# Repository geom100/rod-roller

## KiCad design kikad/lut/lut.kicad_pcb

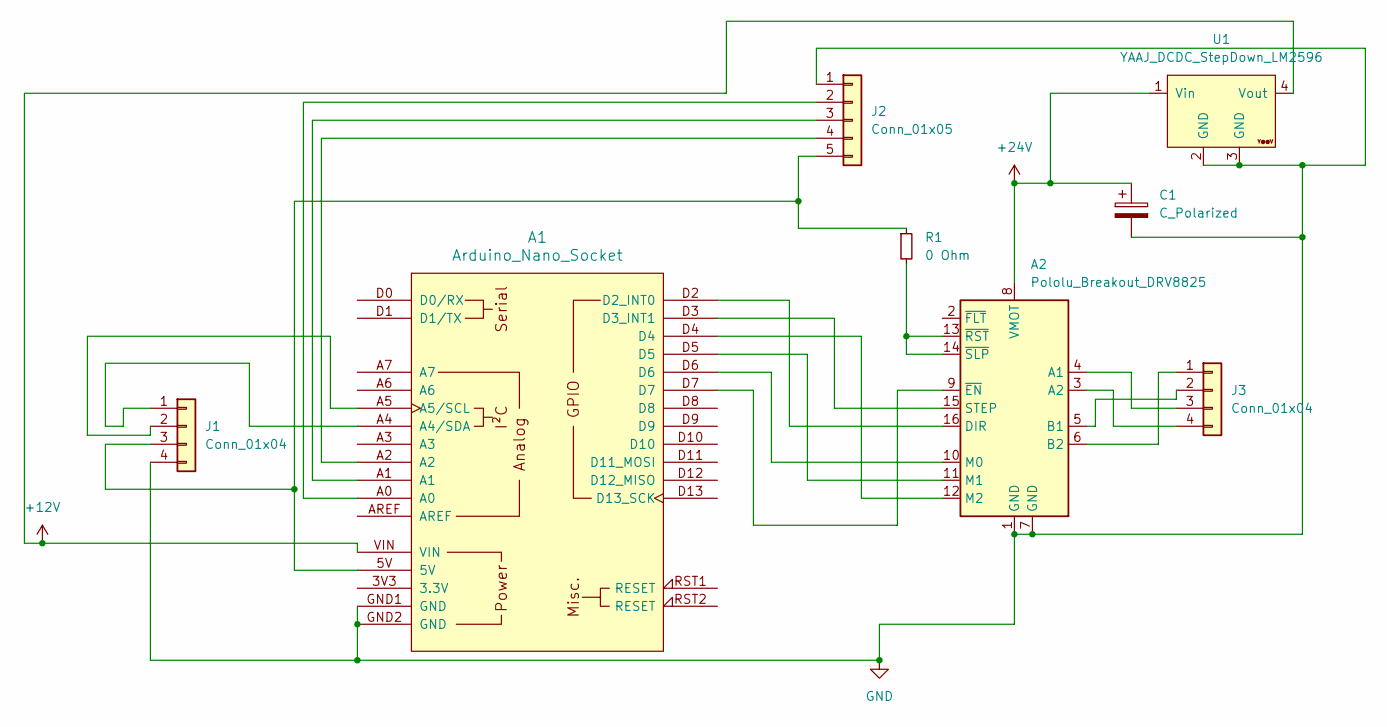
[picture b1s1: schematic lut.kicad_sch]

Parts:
A1: Arduino_Nano_Socket
A2: Pololu_Breakout_DRV8825; Pololu_Breakout-16_15.2x20.3mm
C1: C_Polarized; CP_Radial_D8.0mm_P3.80mm
J1: Conn_01x04; JST_XH_B4B-XH-A_1x04_P2.50mm_Vertical
J2: Conn_01x05; JST_XH_B5B-XH-A_1x05_P2.50mm_Vertical
J3: Conn_01x04; JST_XH_S4B-XH-A_1x04_P2.50mm_Horizontal
R1: 0 Ohm; R_Axial_DIN0207_L6.3mm_D2.5mm_P7.62mm_Horizontal
U1: YAAJ_DCDC_StepDown_LM2596

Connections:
+12V: A1.VIN, U1.4 (Vout)
+24V: A2.8 (VMOT), C1.1, U1.1 (Vin)
GND: A1.GND1 (GND), A1.GND2 (GND), A2.1 (GND), A2.7 (GND), C1.2, J1.4, J2.1, U1.2 (GND), U1.3 (GND)
unnamed: A1.A4 (A4/SDA), J1.1
unnamed: A1.A5 (A5/SCL), J1.2
unnamed: A1.D2 (D2_INT0), A2.16 (DIR)
unnamed: A1.D3 (D3_INT1), A2.15 (STEP)
unnamed: A2.4 (A1), J3.3
unnamed: A2.3 (A2), J3.4
unnamed: A2.5 (B1), J3.2
unnamed: A2.6 (B2), J3.1
unnamed: A1.D6, A2.10 (M0)
unnamed: A1.D5, A2.11 (M1)
unnamed: A1.D4, A2.12 (M2)
unnamed: A1.D7, A2.9 (~EN)
unnamed: A2.13 (~RST), A2.14 (~SLP), R1.2
unnamed: A1.5V, J1.3, J2.5, R1.1
unnamed: A1.A0, J2.2
unnamed: A1.A1, J2.3
unnamed: A1.A2, J2.4

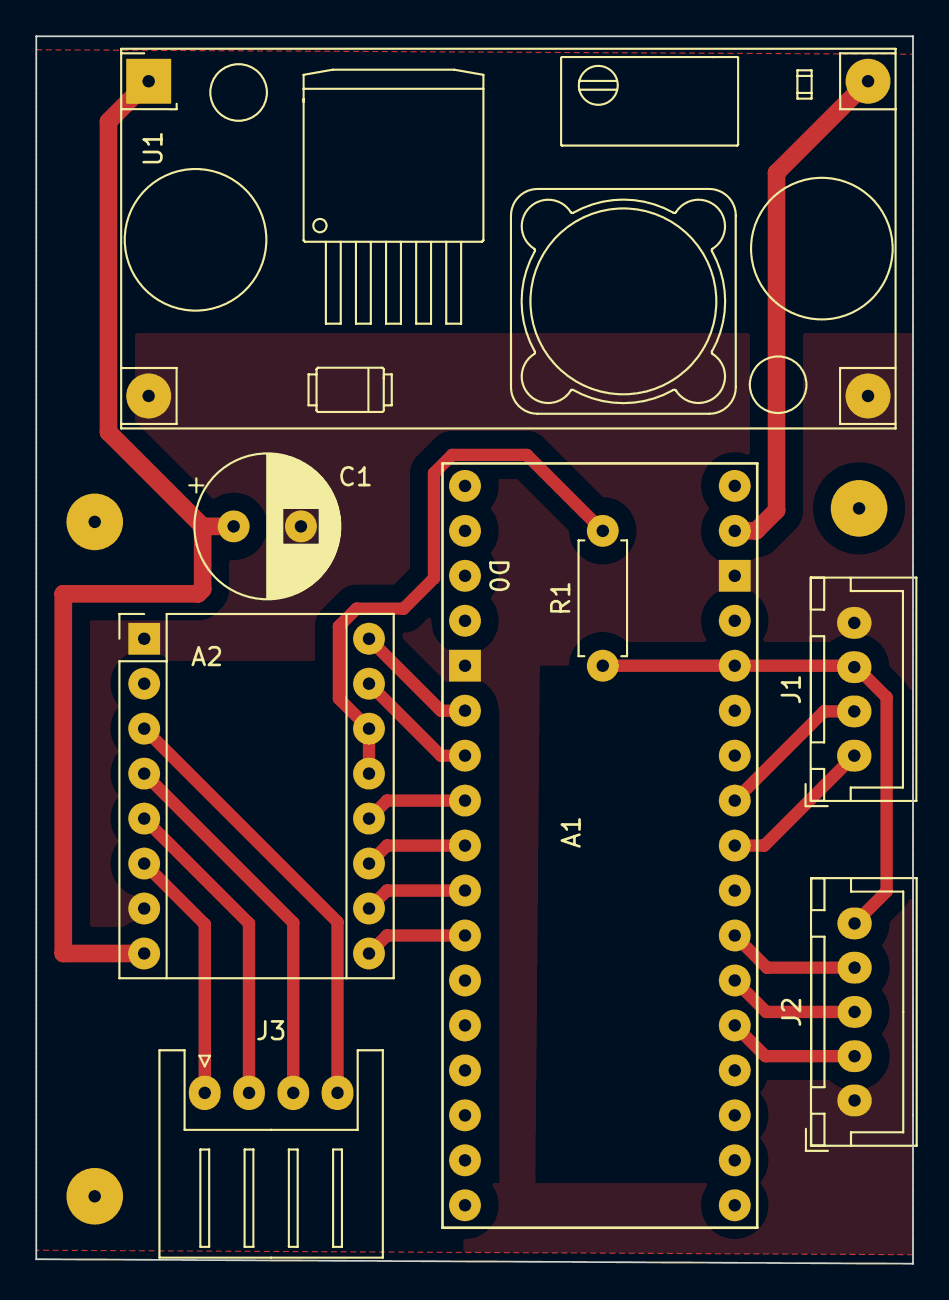
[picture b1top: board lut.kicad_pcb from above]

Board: 2 copper layers, 49.5 x 69.3 mm, 8 parts (0 on the bottom side), 20 nets.

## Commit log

2024-02-08 Initial import of all assets available for now.
2024-02-08 Fix step/dir _state bits.
2024-02-08 Switch dir icon to match encoder dir.
2024-02-09 Add code format definition for VSCode.
2024-02-09 Stepper controlled via Timer2.
2024-02-09 Rename methods to consistent naming scheme.
2024-02-10 Restructure code files. Incapsulate state into ByteState class.
2024-02-10 Use Stepper class to control stepper motor.
2024-02-10 Make direction arrows bigger on screen.
2024-02-11 Enable warnings on build.
2024-02-11 Some code style and licensing info.
2024-02-11 Add LICENSE
2024-02-11 Move LICENSE to project root.
